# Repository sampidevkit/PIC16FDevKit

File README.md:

# PIC16F877A MICROCONTROLLER DEVELOPMENT KIT

## 1. Sơ Đồ Khối

## 2. Sơ Đồ Nguyên Lý

## 3. Vi Điều Khiển Chính PIC16F877A

## 4. Môi Trường Lập Trình, Trình Biên Dịch và Công Cụ Hỗ Trợ

### 4.1. Môi Trường Lập Trình MPLAB X IDE

### 4.2. Trình Biên Dịch MPLAB XC8

## 5. Mạch Nạp Tích Hợp

### 5.1. Nạp Chương Trình Mạch Nạp

### 5.2. Cập Nhật Chương Trình Mạch Nạp

### 5.3 Các Trạng Thái LED Lỗi

## 6. Hướng Dẫn Lập Trình Cơ Bản

## 7. Tài Liệu Kỹ Thuật:
* [PIC16F87XA Datasheet](https://ww1.microchip.com/downloads/aemDocuments/documents/MCU08/ProductDocuments/DataSheets/39582C.pdf).
* [PIC16F87XA Programming Specifications](https://ww1.microchip.com/downloads/en/DeviceDoc/39589C.pdf).

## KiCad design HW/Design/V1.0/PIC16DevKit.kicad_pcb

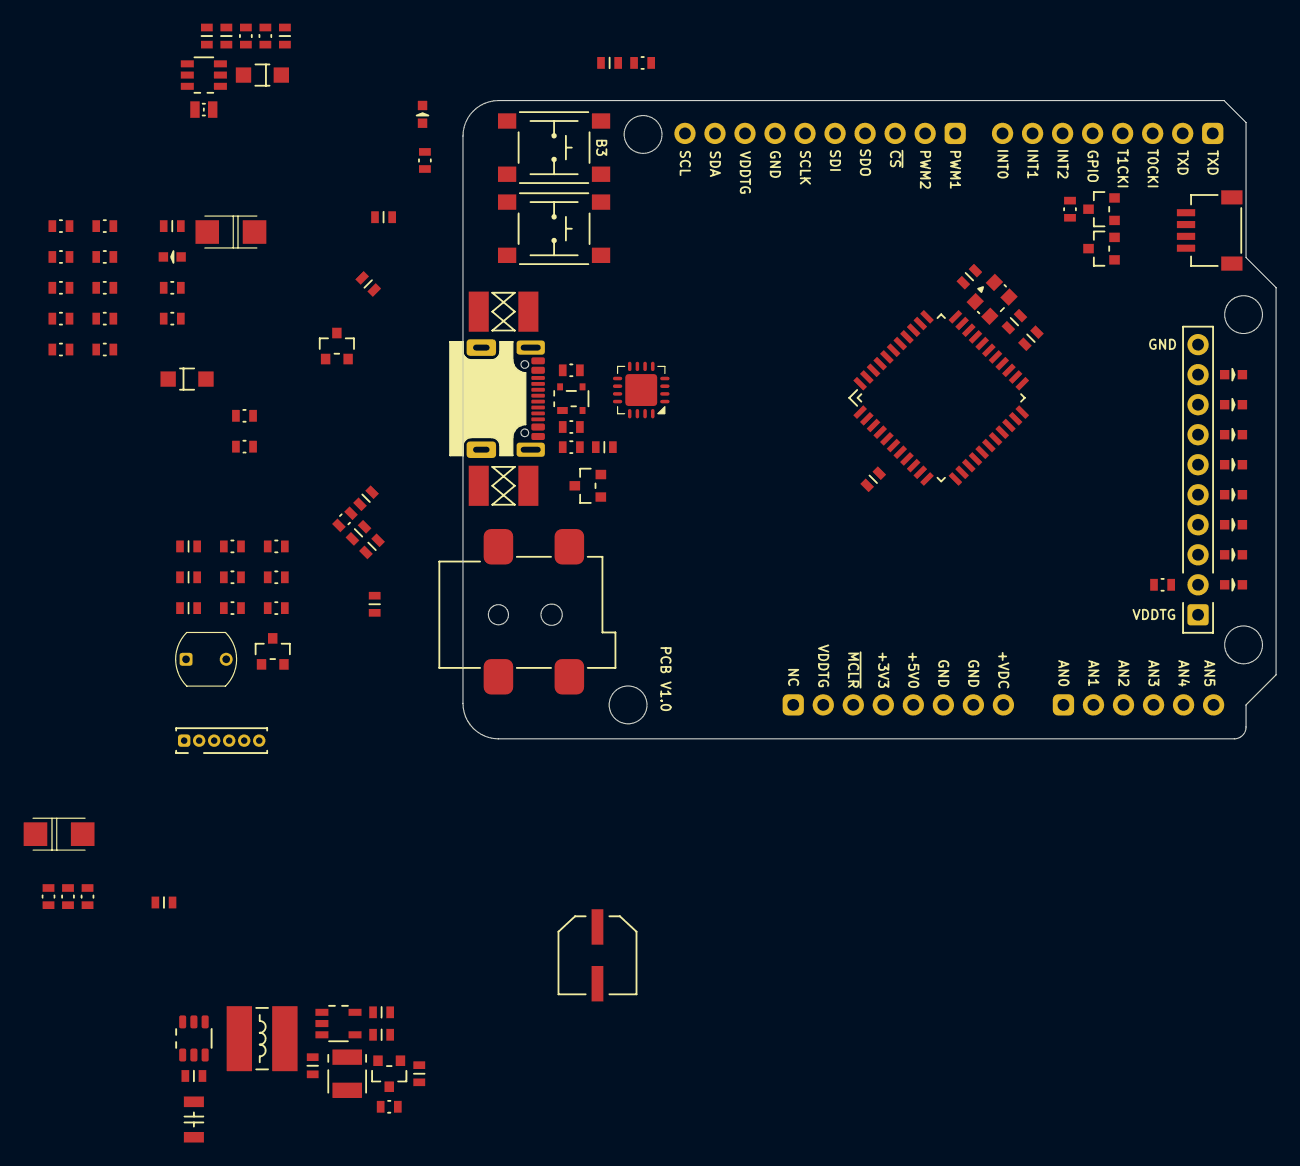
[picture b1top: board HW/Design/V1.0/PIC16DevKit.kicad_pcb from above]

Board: 4 copper layers, 68.8 x 54.0 mm, 102 parts (0 on the bottom side), 82 nets, no tracks yet.

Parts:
BT1: MODE; SW6x6-G
BT2: UBT; SW6x6-G
C1: 220uF; CAP_ELEC-6.6x6.6-DIA6.3
C2: 220uF; CAP1411
C3: 10uF; CAP1206
C4, C5, C6, C14, C17, C18, C19, C20, C22, C25, C26, C32, C37, C38: 100nF; CAP0603
C7, C8, C9, C10, C11, C13, C21, C27: 10uF; CAP0603
C12, C15, C16: 22pF; CAP0603
D1: 15V; DO-214AC
D2, D5: 200mA/0.2VF; SOD-123FL
D3: TVS 5V; SOT143B_NEXT
D4: 1A; DO-214AC
D6: SLED; LED0603
D7: POWER; LED0603
D8: D0; LED0603
D9: D1; LED0603
D10: D2; LED0603
D11: D3; LED0603
D12: D4; LED0603
D13: D5; LED0603
D14: D6; LED0603
D15: D7; LED0603
F1: 1A; FUSE1812
F2: 500mA; FUSE1812
J1: 9V-12V; PJ-002AH-SMT
J2: USB C; USB4105
J3: EXP PORT; HDM1x10x2.54_TH
J4: ICSP; HD-1x6x1.27MM-TH
J5: QWIIC; HDM-1x4x1.0-RA
L1: 10uH/1.4A; IND5852
L2: 10uH/100mA; IND0805
MD1: ARDUINO-UNO-R3
Q1, Q3: SI2301; SOT23
Q5, Q6, Q7: SI2302; SOT23
R1: 52.3K; RES0603
R2, R3, R10, R18, R26, R33: 10K; RES0603
R4: 100K; RES0603
R5: 191K; RES0603
R6, R7, R19, R20, R21, R22, R23, R27: 5.1K; RES0603
R8, R9, R11, R12, R13, R14, R15, R16, R17, R24, R25: 1K; RES0603
R28, R29, R30, R31, R32, R35: 330R; RES0603
R34: 10K; CDS-5MM
U1: LDO 3.3V/300mA; SOT-23-5_MCHP
U2: BUCK 5V/1A; SOT-23-6_MCHP
U3: BOOST 12V; SOT-23-6_MCHP
U4: PIC16F877A; TQFP44-10x10-P0.8
U5: PIC16(L)F1454; VQFN16-P0.65-4x4
U6: SOT23
U10: 20MHz; CDFN3225-4LD-PL-1

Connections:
+3.3V: C8.2, J5.2 (VDD), MD1.4 (+3V3), Q6.1 (G), Q7.1 (G), R21.2, R23.2, U1.5 (VOUT)
+5V: C2.+, C6.1, C13.2, C25.2, C26.2, D5.A, J4.2, L1.2, L2.1, MD1.5 (+5V), Q1.2 (S), Q3.2 (S), R1.2, R4.1, R25.2, U3.5 (IN), U5.16 (VDD)
+VDDTG: C7.2, C9.2, C18.1, C20.1, J3.1, MD1.2 (IOREF), MD1.30 (AREF), Q1.3 (D), R18.1, R19.2, R20.2, R22.2, R27.1, R35.1, U1.1 (VIN), U1.3 (EN), U4.7 (VDD), U4.28 (VDD)
/POWER/USB_N: D3.3 (CH2), J2.A7 (DN1), J2.B7 (DN2), U5.11 (RA1/D-/IOC/PGC2)
/POWER/USB_P: D3.2 (CH1), J2.A6 (DP1), J2.B6 (DP2), U5.12 (RA0/D+/IOC/PGD2)
/POWER/VPP_EN: U3.4 (EN), U5.1 (RA5/SOSCI/T1CKI/PWM2/IOC/CLKIN/OSC1)
/POWER/~VTG_EN: Q1.1 (G), R4.2, U5.7 (RC2/SDO)
/PROGRAMMER/PGC_SDA: J4.4, U5.8 (RC1/SDA/SDI/INT/PGC1)
/PROGRAMMER/PGD_SCL: J4.5, U5.9 (RC0/SCL/SCK/PGD1)
/TARGET MCU/MCU_TXD: R31.2, R32.2, U4.1 (DT/RX/RC7), U4.44 (CK/TX/RC6)
/TARGET MCU/PGC_SDA: MD1.31 (D14/SDA), R27.2, U4.16 (PGC/RB6)
/TARGET MCU/PGD_SCL: MD1.32 (D15/SCL), R19.1, U4.17 (PGD/RB7)
AN0: MD1.9 (AN0), U4.19 (AN0/RA0)
AN1: MD1.10 (AN1), U4.20 (AN1/RA1)
AN2: MD1.11 (AN2), U4.21 (CVREF/VREF-/AN2/RA2)
AN3: MD1.12 (AN3), U4.22 (VREF+/AN3/RA3)
AN4: MD1.13 (AN4/SDA), U4.24 (~SS/C2OUT/AN4/RA5)
AN5: MD1.14 (AN5/SCL), U4.25 (RE0/~RD/AN5)
GND: BT1.3, BT1.4, BT2.3, BT2.4, C1.-, C2.-, C3.2, C4.1, C6.2, C7.1, C8.1, C9.1, C10.1, C11.2, C13.1, C14.2, C15.2, C16.1, C17.2, C18.2, C20.2, C21.1, C22.2, C25.1, C26.1, C27.2, C32.2, C37.1, C38.2, D1.A, D3.1 (GND), D6.K, D7.K, J1.2, J1.3, J2.A1B12 (GND), J2.B1A12 (GND), J2.S1, J2.S2, J2.S3, J2.S4, J3.10, J4.3, J5.0 (EP), J5.1 (GND), MD1.6 (GND), MD1.7 (GND), MD1.29 (GND), Q5.2 (S), R2.1, R3.2, R6.2, R7.1, R9.1, R10.2, R11.1, R12.1, R13.1, R14.1, R15.1, R16.1, R17.1, R33.2, U1.2 (GND), U2.1 (GND), U3.2 (GND), U4.6 (VSS), U4.29 (VSS), U5.13 (VSS), U5.17 (EP), U6.3 (GND), U10.2 (GND1), U10.4 (X2)
GPIO: MD1.19 (D4), U4.15 (RB5)
INT0: MD1.22 (D7), U4.8 (INT/RB0)
INT1: MD1.21 (D6), U4.9 (RB1)
INT2: MD1.20 (D5), U4.10 (RB2)
unnamed: C3.1, C19.2, D1.K, D4.A, F1.2, R8.1
unnamed: D3.4 (CH3), F2.1, J2.A4B9 (VBUS), J2.B4A9 (VBUS)
unnamed: D5.K, R26.2
unnamed: D6.A, R24.1
unnamed: D7.A, R25.1
unnamed: D8.K, R17.2
unnamed: D9.K, R16.2
unnamed: D10.K, R15.2
unnamed: D11.K, R14.2
unnamed: D12.K, R13.2
unnamed: D13.K, R12.2
unnamed: D14.K, R9.2
unnamed: D15.K, R11.2
unnamed: F1.1, J1.1
unnamed: J2.A5 (CC1), R7.2
unnamed: J2.B5 (CC2), R6.1
unnamed: J5.4 (SCL), Q6.2 (S), R21.1
unnamed: J5.3 (SDA), Q7.2 (S), R23.1
unnamed: MD1.15 (D0/RXD), R32.1
unnamed: MD1.16 (D1/TXD), R31.1
unnamed: C19.1, Q3.1 (G), R3.1, R8.2, U2.5 (EN)
unnamed: C38.1, U1.4 (NC/BP)
unnamed: C5.2, U2.6 (BS)
unnamed: R1.1, R2.2, U2.4 (FB)
unnamed: C5.1, L1.1, U2.2 (SW)
unnamed: C12.2, R5.2, R10.1, U3.3 (FB)
unnamed: D2.A, L2.2, U3.1 (SW)
unnamed: R28.2, U5.5 (RC4/TX/CK)
unnamed: R30.2, U5.4 (RC5/T0CKI/RX/DT/PWM1)
unnamed: C27.1, U5.10 (VUSB3V3)
unnamed: C21.2, R34.2, R35.2, U6.1 (VDD)
unnamed: C15.1, U4.30 (OSC1/CLKI), U10.3 (GND2)
unnamed: C16.2, U4.31 (OSC2/CLKO), U10.1 (X1)
PWM1: MD1.23 (D8), U4.36 (CCP1/RC2)
PWM2: MD1.24 (D9), U4.35 (T1OSI/CCP2/RC1)
RD0: D8.A, J3.9, U4.5 (RD7/PSP7)
RD1: D9.A, J3.8, U4.4 (RD6/PSP6)
RD2: D10.A, J3.7, U4.3 (RD5/PSP5)
RD3: D11.A, J3.6, U4.2 (RD4/PSP4)
RD4: D12.A, J3.5, U4.41 (RD3/PSP3)
RD5: D13.A, J3.4, U4.40 (RD2/PSP2)
RD6: D14.A, J3.3, U4.39 (RD1/PSP1)
RD7: D15.A, J3.2, U4.38 (RD0/PSP0)
SCL: Q6.3 (D), R22.1
SCLK: MD1.28 (D13/SCLK), U4.37 (SCK/SCL/RC3)
SDA: Q7.3 (D), R20.1
SDI: MD1.27 (D12/MISO), U4.42 (SDI/SDA/RC4)
SDO: MD1.26 (D11/MOSI), U4.43 (SDO/RC5)
SLED: R24.2, U5.6 (RC3/PWM2/SS/CLKR)
T0CKI: MD1.17 (D2), U4.23 (C1OUT/T0CKI/RA4)
T1CKI: MD1.18 (D3), U4.32 (T1OSO/T1CKI/RC0)
TEMP: C14.1, C22.1, R33.1, R34.1, U4.26 (RE1/~WR/AN6), U6.2 (VOUT)
VBUS: C10.2, F2.2, Q3.3 (D)
VDC: C1.+, C4.2, D4.K, MD1.8 (VIN), U2.3 (IN)
VPP: C11.1, C12.1, D2.K, R5.1, R29.1
~CS: MD1.25 (D10/~SS), U4.14 (RB4)
~PG_MCLR: BT1.1, BT1.2, C32.1, J4.1, R26.1
~TG_MCLR: C37.2, MD1.3 (RESET), Q5.1 (G), Q5.3 (D), R29.2, U4.18 (~MCLR/VPP), U5.2 (RA4/SOSCO/T1G/SDO/IOC/CLKOUT/OSC2/CLKR)
~UBT: BT2.1, BT2.2, C17.1, R18.2, U4.11 (PGM/RB3)

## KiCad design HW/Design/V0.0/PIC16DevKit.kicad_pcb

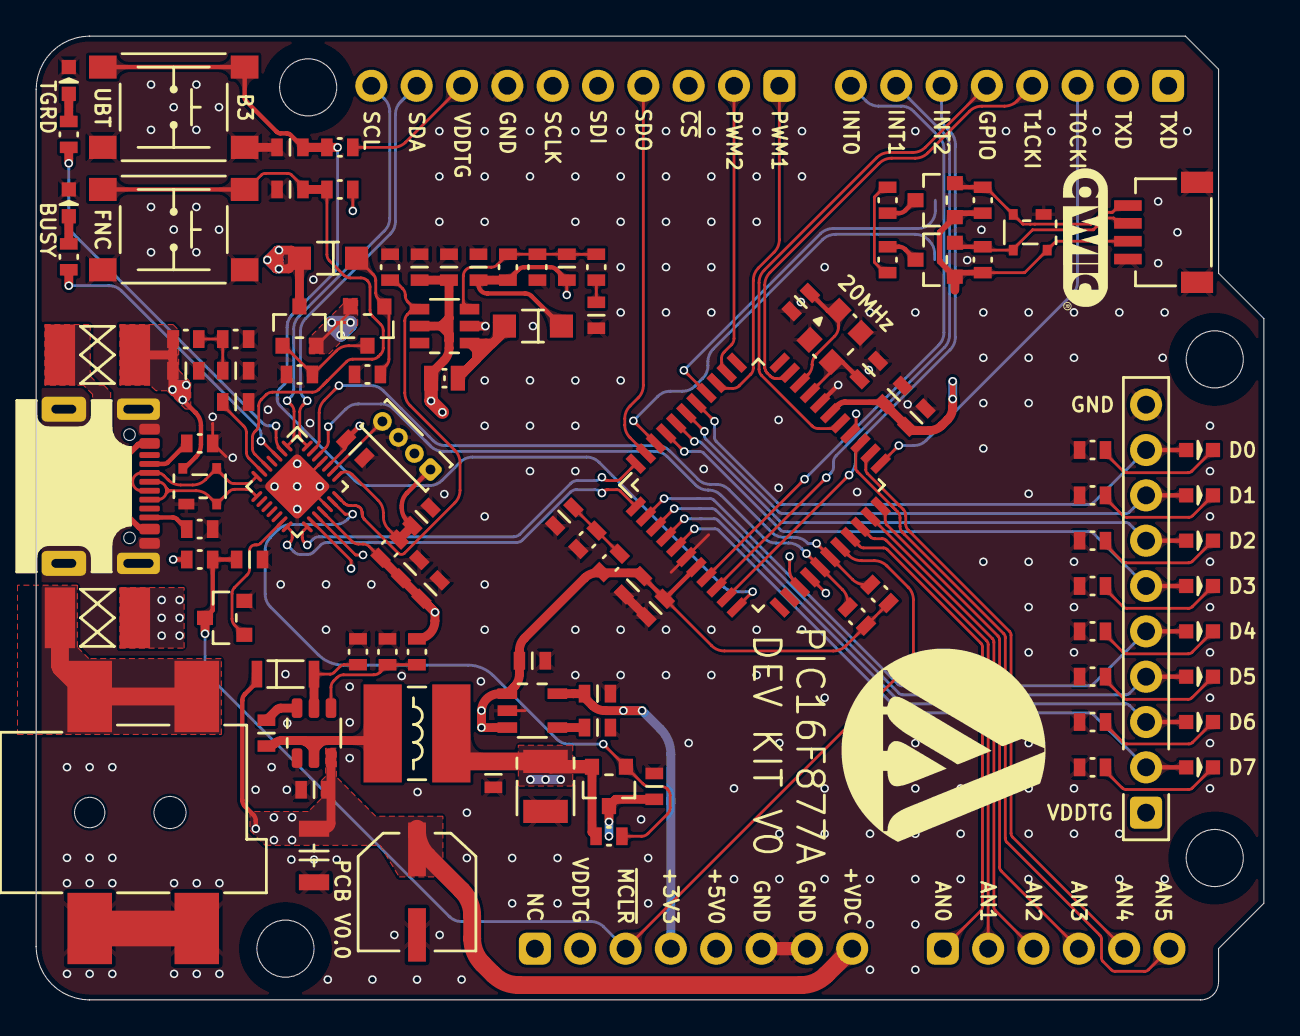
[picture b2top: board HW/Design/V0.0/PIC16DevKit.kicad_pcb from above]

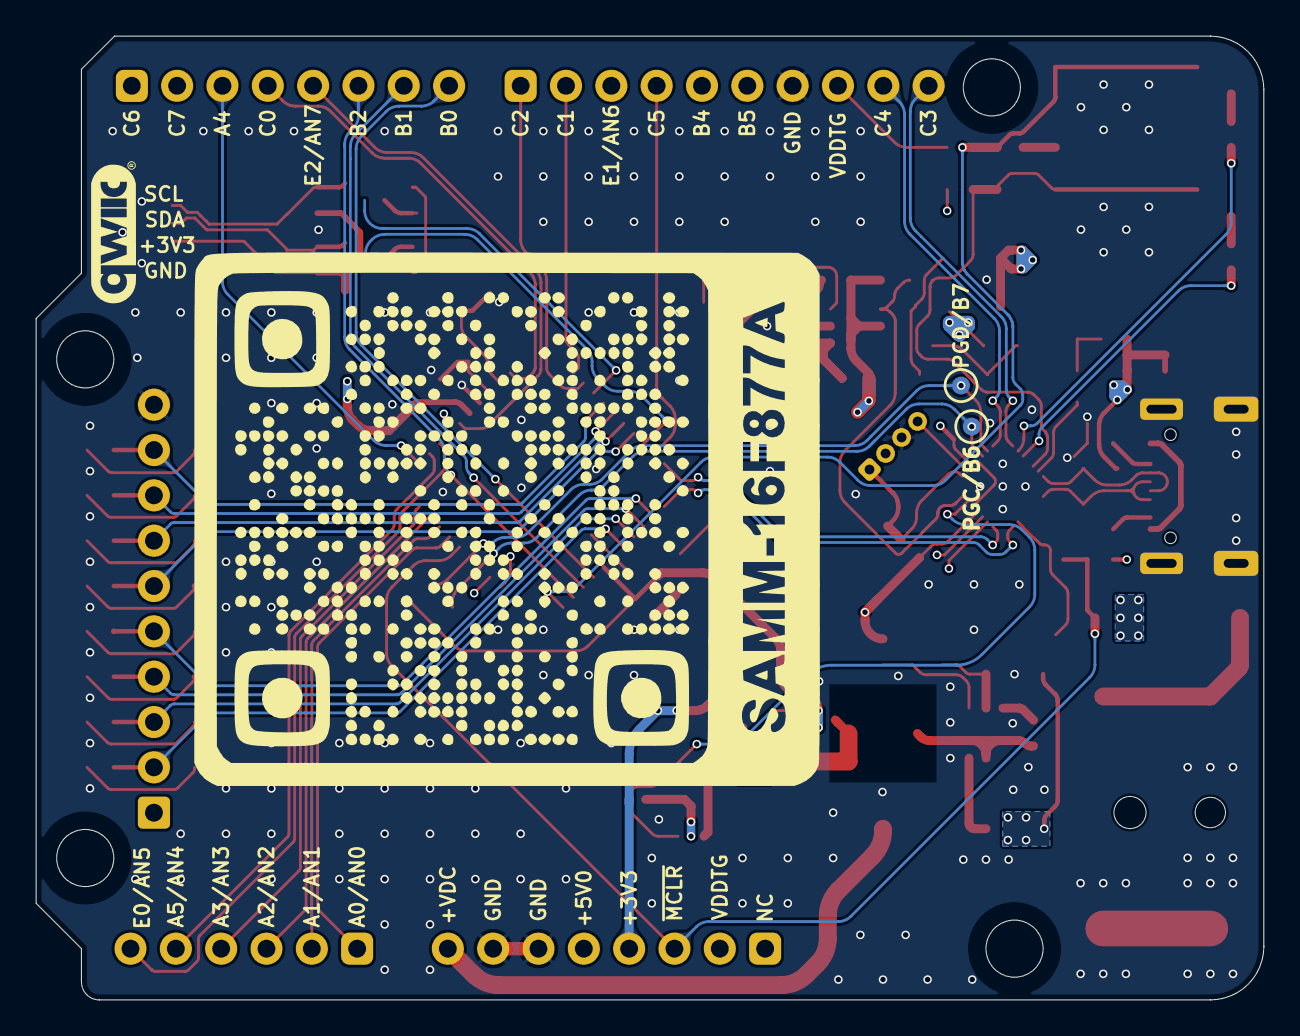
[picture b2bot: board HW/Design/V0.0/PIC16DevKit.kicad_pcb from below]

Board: 4 copper layers, 68.8 x 54.0 mm, 109 parts (2 on the bottom side), 84 nets.

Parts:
BT1: FNC; SW6x6-G
BT2: UBT; SW6x6-G
C1: 220uF; CAP_ELEC-6.6x6.6-DIA6.3
C2: 220uF; CAP1411
C3: 10uF/16V; CAP1206
C4, C5, C6, C14, C17, C18, C20, C22, C25, C26, C32, C37, C38, C39, C40, C41: 100nF; CAP0603
C7, C8, C9, C10, C11, C13, C19, C21, C27: 10uF; CAP0603
C12, C15, C16: 22pF; CAP0603
C23: 470nF; CAP0603
D1: 5V1; SOD80C-LL34
D2, D4: 200mA/0.2VF; SOD-123FL
D3, D5: TVS 5V; SOT143B_NEXT
D6: TGRD; LED0603
D7: BUSY; LED0603
D8: D0; LED0603
D9: D1; LED0603
D10: D2; LED0603
D11: D3; LED0603
D12: D4; LED0603
D13: D5; LED0603
D14: D6; LED0603
D15: D7; LED0603
F1: 1A; FUSE1812
F2: 500mA; FUSE1812
J1: 9V-12V; PJ-002AH-SMT
J2: USB C; USB4105
J3: EXP PORT; HDM1x10x2.54_TH
J4: SIL04; HD-1x4x1.27MM-TH
J5: QWIIC; HDM-1x4x1.0-RA
L1: 10uH/1.4A; IND5852
L2: 10uH/100mA; IND0805
MD1: ARDUINO-UNO-R3
Q1, Q3: SI2301; SOT23
Q4: 2N3906; SOT23
Q5, Q6, Q7: SI2302; SOT23
R1: 52.3K, 1%; RES0603
R2, R10, R36: 10K, 1%; RES0603
R3, R8, R9, R31: 100K; RES0603
R4, R18, R23, R26: 10K; RES0603
R5: 191K, 1%; RES0603
R6, R7, R19, R21, R22, R27, R28, R30, R32, R35: 5.1K, 1%; RES0603
R11, R12, R13, R14, R15, R16, R17, R20, R24, R25, R29: 330R; RES0603
R33, R34: 47K, 1%; RES0603
TP1: PGC/B6; TP1MM
TP2: PGD/B7; TP1MM
U1: LDO 3.3V/300mA; SOT-23-5_MCHP
U2: MT1470; SOT-23-6_MCHP
U3: MT3608; SOT-23-6_MCHP
U4: PIC16F877A; TQFP44-10x10-P0.8
U5: AVRxxDU28; VQFN28-4x4-EP
U10: 20MHz; CDFN3225-4LD-PL-1

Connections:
+3.3V: C8.1, D5.4 (CH3), J5.2 (VDD), MD1.4 (+3V3), Q6.1 (G), Q7.1 (G), R28.1, R30.1, U1.5 (VOUT)
+5V: C2.+, C6.1, C13.1, C14.1, C25.1, C26.1, C27.1, J4.2, L1.2, L2.1, MD1.5 (+5V), Q1.2 (S), Q3.2 (S), Q4.2 (E), R1.1, R4.1, R23.1, R26.1, U3.5 (IN), U5.18 (VDD), U5.24 (VDD)
+VDDTG: C7.1, C9.1, C18.1, C19.1, C20.1, C21.1, J3.1, MD1.2 (IOREF), MD1.30 (AREF), Q1.3 (D), R18.1, R19.1, R21.1, R22.1, R27.1, R34.1, U1.1 (VIN), U1.3 (EN), U4.7 (VDD), U4.28 (VDD)
/POWER/USB_N: D3.3 (CH2), J2.A7 (DN1), J2.B7 (DN2), U5.7 (DM)
/POWER/USB_P: D3.2 (CH1), J2.A6 (DP1), J2.B6 (DP2), U5.8 (DP)
/POWER/VBUS_DIV: C39.1, R32.1, R33.2, U5.9 (PC3/ACINP/AIN6)
/POWER/VDDTG_DIV: C40.1, R34.2, R35.1, U5.11 (PD1/AIN8)
/POWER/VPP_DIV: C41.1, R36.2, U5.10 (PD0/ACINN/AIN7)
/POWER/VPP_EN: R31.1, U3.4 (EN), U5.21 (PF1/ANI16/XTAL32K2)
/POWER/~VTG_EN: Q1.1 (G), R4.2, U5.20 (PF0/AIN15/XTAL32K1)
/PROGRAMMER/LED_BUSY: R25.1, U5.3 (PA5/MISO/A2RX0/AIN3)
/PROGRAMMER/LED_TGRDY: R24.1, U5.2 (PA4/MOSI/A2TX0/AIN2)
/PROGRAMMER/PG_UPDI: J4.4, U5.23 (PF7/UPDI)
/PROGRAMMER/RXD0: U4.44 (CK/TX/RC6), U5.15 (PD5/AMISO/A3RX0/AIN12)
/PROGRAMMER/RXD1: MD1.16 (D1/TXD), U5.17 (PD7/RX1/AINN/AIN14)
/PROGRAMMER/SCL: MD1.32 (D15/SCL), Q6.3 (D), R22.2, U4.37 (SCK/SCL/RC3), U5.1 (PA3/A1RX0/SCL/AIN1)
/PROGRAMMER/SDA: MD1.31 (D14/SDA), Q7.3 (D), R21.2, U4.42 (SDI/SDA/RC4), U5.28 (PA2/A1TX0/SDA/AIN0)
/PROGRAMMER/TG_MCLR: Q5.1 (G), U5.13 (PD3/ACINN/AIN10)
/PROGRAMMER/TG_PGC: R19.2, TP1.1, U4.16 (PGC/RB6), U5.26 (PA0/TX0/ASDA/XTALHF1)
/PROGRAMMER/TG_PGD: R27.2, TP2.1, U4.17 (PGD/RB7), U5.27 (PA1/RX0/ASCL/XTALHF2)
/PROGRAMMER/TXD0: U4.1 (DT/RX/RC7), U5.14 (PD4/AMOSI/A3TX0/AIN11)
/PROGRAMMER/TXD1: MD1.15 (D0/RXD), U5.16 (PD6/ASCLK/TX1/ACINP/AIN13)
/PROGRAMMER/~BT_FNC: BT1.1, BT1.2, C22.1, R23.2, U5.5 (PA7/ACOUT/AIN5)
/PROGRAMMER/~PG_RESET: C32.2, J4.1, R26.2, U5.22 (PF6/~RESET)
/PROGRAMMER/~TG_MCLR: C37.1, MD1.3 (RESET), Q5.3 (D), R29.2, U4.18 (~MCLR/VPP)
/TARGET MCU/AN0: MD1.9 (AN0), U4.19 (AN0/RA0)
/TARGET MCU/AN1: MD1.10 (AN1), U4.20 (AN1/RA1)
/TARGET MCU/AN2: MD1.11 (AN2), U4.21 (CVREF/VREF-/AN2/RA2)
/TARGET MCU/AN3: MD1.12 (AN3), U4.22 (VREF+/AN3/RA3)
/TARGET MCU/AN4: MD1.13 (AN4/SDA), U4.24 (~SS/C2OUT/AN4/RA5)
/TARGET MCU/AN5: MD1.14 (AN5/SCL), U4.25 (RE0/~RD/AN5)
/TARGET MCU/GPIO: MD1.19 (D4), U4.27 (RE2/~CS/AN7)
/TARGET MCU/INT0: MD1.22 (D7), U4.8 (INT/RB0)
/TARGET MCU/INT1: MD1.21 (D6), U4.9 (RB1)
/TARGET MCU/INT2: MD1.20 (D5), U4.10 (RB2)
/TARGET MCU/PWM1: MD1.23 (D8), U4.36 (CCP1/RC2)
/TARGET MCU/PWM2: MD1.24 (D9), U4.35 (T1OSI/CCP2/RC1)
/TARGET MCU/RD0: D8.A, J3.9, U4.38 (RD0/PSP0)
/TARGET MCU/RD1: D9.A, J3.8, U4.39 (RD1/PSP1)
/TARGET MCU/RD2: D10.A, J3.7, U4.40 (RD2/PSP2)
/TARGET MCU/RD3: D11.A, J3.6, U4.41 (RD3/PSP3)
/TARGET MCU/RD4: D12.A, J3.5, U4.2 (RD4/PSP4)
/TARGET MCU/RD5: D13.A, J3.4, U4.3 (RD5/PSP5)
/TARGET MCU/RD6: D14.A, J3.3, U4.4 (RD6/PSP6)
/TARGET MCU/RD7: D15.A, J3.2, U4.5 (RD7/PSP7)
/TARGET MCU/SCLK: MD1.28 (D13/SCLK), U4.15 (RB5)
/TARGET MCU/SDI: MD1.27 (D12/MISO), U4.14 (RB4)
/TARGET MCU/SDO: MD1.26 (D11/MOSI), U4.43 (SDO/RC5)
/TARGET MCU/T0CKI: MD1.17 (D2), U4.23 (C1OUT/T0CKI/RA4)
/TARGET MCU/T1CKI: MD1.18 (D3), U4.32 (T1OSO/T1CKI/RC0)
/TARGET MCU/~CS: MD1.25 (D10/~SS), U4.26 (RE1/~WR/AN6)
/TARGET MCU/~UBT: BT2.1, BT2.2, C17.2, R18.2, U4.11 (PGM/RB3)
GND: BT1.3, BT1.4, BT2.3, BT2.4, C1.-, C2.-, C3.2, C4.2, C6.2, C7.2, C8.2, C9.2, C10.2, C11.2, C13.2, C14.2, C15.1, C16.1, C17.1, C18.2, C19.2, C20.2, C21.2, C22.2, C23.2, C25.2, C26.2, C27.2, C32.1, C37.2, C38.2, C39.2, C40.2, C41.2, D3.1 (GND), D5.1 (GND), D6.K, D7.K, J1.2, J1.3, J2.A1B12 (GND), J2.B1A12 (GND), J2.S1, J2.S2, J2.S3, J2.S4, J3.10, J4.3, J5.0 (EP), J5.1 (GND), MD1.6 (GND), MD1.7 (GND), MD1.29 (GND), Q5.2 (S), R2.2, R3.2, R6.2, R7.2, R8.2, R9.2, R10.2, R11.1, R12.1, R13.1, R14.1, R15.1, R16.1, R17.1, R20.1, R31.2, R32.2, R35.2, U1.2 (GND), U2.1 (GND), U3.2 (GND), U4.6 (VSS), U4.29 (VSS), U5.19 (GND), U5.25 (GND), U5.29 (EP), U10.2 (GND1), U10.4 (X2)
unnamed: D5.2 (CH1), J5.4 (SCL), Q6.2 (S), R28.2
unnamed: D5.3 (CH2), J5.3 (SDA), Q7.2 (S), R30.2
unnamed: D6.A, R24.2
unnamed: D7.A, R25.2
unnamed: D8.K, R20.2
unnamed: D9.K, R17.2
unnamed: D10.K, R16.2
unnamed: D11.K, R15.2
unnamed: D12.K, R14.2
unnamed: D13.K, R13.2
unnamed: D14.K, R12.2
unnamed: D15.K, R11.2
unnamed: F1.1, J1.1
unnamed: F2.1, J2.A4B9 (VBUS), J2.B4A9 (VBUS)
unnamed: J2.A5 (CC1), R7.1
unnamed: J2.B5 (CC2), R6.1
unnamed: Q3.1 (G), Q4.3 (C), R9.1
unnamed: D4.K, Q4.1 (B), R8.1
unnamed: C38.1, U1.4 (NC/BP)
unnamed: C5.2, U2.6 (BS)
unnamed: D1.A, R3.1, U2.5 (EN)
unnamed: R1.2, R2.1, U2.4 (FB)
unnamed: C5.1, L1.1, U2.2 (SW)
unnamed: C12.2, R5.2, R10.1, R36.1, U3.3 (FB)
unnamed: D2.A, L2.2, U3.1 (SW)
unnamed: C23.1, U5.6 (VUSB)
unnamed: C15.2, U4.30 (OSC1/CLKI), U10.3 (GND2)
unnamed: C16.2, U4.31 (OSC2/CLKO), U10.1 (X1)
VBUS: C10.1, D3.4 (CH3), D4.A, F2.2, Q3.3 (D), R33.1
VDC: C1.+, C3.1, C4.1, D1.K, F1.2, MD1.8 (VIN), U2.3 (IN)
VPP: C11.1, C12.1, D2.K, R5.1, R29.1

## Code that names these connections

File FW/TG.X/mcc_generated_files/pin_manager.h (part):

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#define RA0_SetHigh()            do { LATAbits.LATA0 = 1; } while(0)
#define RA0_SetLow()             do { LATAbits.LATA0 = 0; } while(0)
#define RA0_Toggle()             do { LATAbits.LATA0 = ~LATAbits.LATA0; } while(0)
#define RA0_GetValue()              PORTAbits.RA0
#define RA0_SetDigitalInput()    do { TRISAbits.TRISA0 = 1; } while(0)
#define RA0_SetDigitalOutput()   do { TRISAbits.TRISA0 = 0; } while(0)
#define RA0_SetPullup()             do { WPUAbits.WPUA0 = 1; } while(0)
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#define RA1_SetHigh()            do { LATAbits.LATA1 = 1; } while(0)
#define RA1_SetLow()             do { LATAbits.LATA1 = 0; } while(0)
#define RA1_Toggle()             do { LATAbits.LATA1 = ~LATAbits.LATA1; } while(0)
#define RA1_GetValue()              PORTAbits.RA1
#define RA1_SetDigitalInput()    do { TRISAbits.TRISA1 = 1; } while(0)
#define RA1_SetDigitalOutput()   do { TRISAbits.TRISA1 = 0; } while(0)
#define RA1_SetPullup()             do { WPUAbits.WPUA1 = 1; } while(0)
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// get/set ULED aliases
#define ULED_TRIS                 TRISAbits.TRISA2
#define ULED_LAT                  LATAbits.LATA2
#define ULED_PORT                 PORTAbits.RA2
#define ULED_WPU                  WPUAbits.WPUA2
#define ULED_OD                   ODCONAbits.ODA2
#define ULED_ANS                  ANSELAbits.ANSA2
#define ULED_SetHigh()            do { LATAbits.LATA2 = 1; } while(0)
#define ULED_SetLow()             do { LATAbits.LATA2 = 0; } while(0)
#define ULED_Toggle()             do { LATAbits.LATA2 = ~LATAbits.LATA2; } while(0)
#define ULED_GetValue()           PORTAbits.RA2
#define ULED_SetDigitalInput()    do { TRISAbits.TRISA2 = 1; } while(0)
#define ULED_SetDigitalOutput()   do { TRISAbits.TRISA2 = 0; } while(0)
#define ULED_SetPullup()          do { WPUAbits.WPUA2 = 1; } while(0)
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#define RA4_SetHigh()            do { LATAbits.LATA4 = 1; } while(0)
#define RA4_SetLow()             do { LATAbits.LATA4 = 0; } while(0)
#define RA4_Toggle()             do { LATAbits.LATA4 = ~LATAbits.LATA4; } while(0)
#define RA4_GetValue()              PORTAbits.RA4
#define RA4_SetDigitalInput()    do { TRISAbits.TRISA4 = 1; } while(0)
#define RA4_SetDigitalOutput()   do { TRISAbits.TRISA4 = 0; } while(0)
#define RA4_SetPullup()             do { WPUAbits.WPUA4 = 1; } while(0)
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#define RA5_SetHigh()            do { LATAbits.LATA5 = 1; } while(0)
#define RA5_SetLow()             do { LATAbits.LATA5 = 0; } while(0)
#define RA5_Toggle()             do { LATAbits.LATA5 = ~LATAbits.LATA5; } while(0)
#define RA5_GetValue()              PORTAbits.RA5
#define RA5_SetDigitalInput()    do { TRISAbits.TRISA5 = 1; } while(0)
#define RA5_SetDigitalOutput()   do { TRISAbits.TRISA5 = 0; } while(0)
#define RA5_SetPullup()             do { WPUAbits.WPUA5 = 1; } while(0)
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// get/set SCK aliases
#define SCK_TRIS                 TRISBbits.TRISB4
#define SCK_LAT                  LATBbits.LATB4
#define SCK_PORT                 PORTBbits.RB4
#define SCK_WPU                  WPUBbits.WPUB4
#define SCK_OD                   ODCONBbits.ODB4
#define SCK_ANS                  ANSELBbits.ANSB4
#define SCK_SetHigh()            do { LATBbits.LATB4 = 1; } while(0)
#define SCK_SetLow()             do { LATBbits.LATB4 = 0; } while(0)
#define SCK_Toggle()             do { LATBbits.LATB4 = ~LATBbits.LATB4; } while(0)
#define SCK_GetValue()           PORTBbits.RB4
#define SCK_SetDigitalInput()    do { TRISBbits.TRISB4 = 1; } while(0)
#define SCK_SetDigitalOutput()   do { TRISBbits.TRISB4 = 0; } while(0)
#define SCK_SetPullup()          do { WPUBbits.WPUB4 = 1; } while(0)
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#define RB5_SetHigh()            do { LATBbits.LATB5 = 1; } while(0)
#define RB5_SetLow()             do { LATBbits.LATB5 = 0; } while(0)
#define RB5_Toggle()             do { LATBbits.LATB5 = ~LATBbits.LATB5; } while(0)
#define RB5_GetValue()              PORTBbits.RB5
#define RB5_SetDigitalInput()    do { TRISBbits.TRISB5 = 1; } while(0)
#define RB5_SetDigitalOutput()   do { TRISBbits.TRISB5 = 0; } while(0)
#define RB5_SetPullup()             do { WPUBbits.WPUB5 = 1; } while(0)
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#define RB6_SetHigh()            do { LATBbits.LATB6 = 1; } while(0)
#define RB6_SetLow()             do { LATBbits.LATB6 = 0; } while(0)
#define RB6_Toggle()             do { LATBbits.LATB6 = ~LATBbits.LATB6; } while(0)
#define RB6_GetValue()              PORTBbits.RB6
#define RB6_SetDigitalInput()    do { TRISBbits.TRISB6 = 1; } while(0)
#define RB6_SetDigitalOutput()   do { TRISBbits.TRISB6 = 0; } while(0)
#define RB6_SetPullup()             do { WPUBbits.WPUB6 = 1; } while(0)
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// get/set GPIO1 aliases
#define GPIO1_TRIS                 TRISBbits.TRISB7
#define GPIO1_LAT                  LATBbits.LATB7
#define GPIO1_PORT                 PORTBbits.RB7
#define GPIO1_WPU                  WPUBbits.WPUB7
#define GPIO1_OD                   ODCONBbits.ODB7
#define GPIO1_ANS                  ANSELBbits.ANSB7
#define GPIO1_SetHigh()            do { LATBbits.LATB7 = 1; } while(0)
#define GPIO1_SetLow()             do { LATBbits.LATB7 = 0; } while(0)
#define GPIO1_Toggle()             do { LATBbits.LATB7 = ~LATBbits.LATB7; } while(0)
#define GPIO1_GetValue()           PORTBbits.RB7
#define GPIO1_SetDigitalInput()    do { TRISBbits.TRISB7 = 1; } while(0)
#define GPIO1_SetDigitalOutput()   do { TRISBbits.TRISB7 = 0; } while(0)
#define GPIO1_SetPullup()          do { WPUBbits.WPUB7 = 1; } while(0)
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// get/set NCS aliases
#define NCS_TRIS                 TRISCbits.TRISC0
#define NCS_LAT                  LATCbits.LATC0
#define NCS_PORT                 PORTCbits.RC0
#define NCS_WPU                  WPUCbits.WPUC0
#define NCS_OD                   ODCONCbits.ODC0
#define NCS_ANS                  ANSELCbits.ANSC0
#define NCS_SetHigh()            do { LATCbits.LATC0 = 1; } while(0)
#define NCS_SetLow()             do { LATCbits.LATC0 = 0; } while(0)
#define NCS_Toggle()             do { LATCbits.LATC0 = ~LATCbits.LATC0; } while(0)
#define NCS_GetValue()           PORTCbits.RC0
#define NCS_SetDigitalInput()    do { TRISCbits.TRISC0 = 1; } while(0)
#define NCS_SetDigitalOutput()   do { TRISCbits.TRISC0 = 0; } while(0)
#define NCS_SetPullup()          do { WPUCbits.WPUC0 = 1; } while(0)
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// get/set SDO aliases
#define SDO_TRIS                 TRISCbits.TRISC1
#define SDO_LAT                  LATCbits.LATC1
#define SDO_PORT                 PORTCbits.RC1
#define SDO_WPU                  WPUCbits.WPUC1
#define SDO_OD                   ODCONCbits.ODC1
#define SDO_ANS                  ANSELCbits.ANSC1
#define SDO_SetHigh()            do { LATCbits.LATC1 = 1; } while(0)
#define SDO_SetLow()             do { LATCbits.LATC1 = 0; } while(0)
#define SDO_Toggle()             do { LATCbits.LATC1 = ~LATCbits.LATC1; } while(0)
#define SDO_GetValue()           PORTCbits.RC1
#define SDO_SetDigitalInput()    do { TRISCbits.TRISC1 = 1; } while(0)
#define SDO_SetDigitalOutput()   do { TRISCbits.TRISC1 = 0; } while(0)
#define SDO_SetPullup()          do { WPUCbits.WPUC1 = 1; } while(0)
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// get/set SDI aliases
#define SDI_TRIS                 TRISCbits.TRISC2
#define SDI_LAT                  LATCbits.LATC2
#define SDI_PORT                 PORTCbits.RC2
#define SDI_WPU                  WPUCbits.WPUC2
#define SDI_OD                   ODCONCbits.ODC2
#define SDI_ANS                  ANSELCbits.ANSC2
#define SDI_SetHigh()            do { LATCbits.LATC2 = 1; } while(0)
#define SDI_SetLow()             do { LATCbits.LATC2 = 0; } while(0)
#define SDI_Toggle()             do { LATCbits.LATC2 = ~LATCbits.LATC2; } while(0)
#define SDI_GetValue()           PORTCbits.RC2
#define SDI_SetDigitalInput()    do { TRISCbits.TRISC2 = 1; } while(0)
#define SDI_SetDigitalOutput()   do { TRISCbits.TRISC2 = 0; } while(0)
#define SDI_SetPullup()          do { WPUCbits.WPUC2 = 1; } while(0)
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// get/set SAN0 aliases
#define SAN0_TRIS                 TRISCbits.TRISC3
#define SAN0_LAT                  LATCbits.LATC3
#define SAN0_PORT                 PORTCbits.RC3
#define SAN0_WPU                  WPUCbits.WPUC3
#define SAN0_OD                   ODCONCbits.ODC3
#define SAN0_ANS                  ANSELCbits.ANSC3
#define SAN0_SetHigh()            do { LATCbits.LATC3 = 1; } while(0)
#define SAN0_SetLow()             do { LATCbits.LATC3 = 0; } while(0)
#define SAN0_Toggle()             do { LATCbits.LATC3 = ~LATCbits.LATC3; } while(0)
#define SAN0_GetValue()           PORTCbits.RC3
#define SAN0_SetDigitalInput()    do { TRISCbits.TRISC3 = 1; } while(0)
#define SAN0_SetDigitalOutput()   do { TRISCbits.TRISC3 = 0; } while(0)
#define SAN0_SetPullup()          do { WPUCbits.WPUC3 = 1; } while(0)
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// get/set GPIO3 aliases
#define GPIO3_TRIS                 TRISCbits.TRISC4
#define GPIO3_LAT                  LATCbits.LATC4
#define GPIO3_PORT                 PORTCbits.RC4
#define GPIO3_WPU                  WPUCbits.WPUC4
#define GPIO3_OD                   ODCONCbits.ODC4
#define GPIO3_SetHigh()            do { LATCbits.LATC4 = 1; } while(0)
#define GPIO3_SetLow()             do { LATCbits.LATC4 = 0; } while(0)
#define GPIO3_Toggle()             do { LATCbits.LATC4 = ~LATCbits.LATC4; } while(0)
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
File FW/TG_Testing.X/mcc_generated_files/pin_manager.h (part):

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// get/set BLED aliases
#define BLED_TRIS                 TRISAbits.TRISA1
#define BLED_LAT                  LATAbits.LATA1
#define BLED_PORT                 PORTAbits.RA1
#define BLED_WPU                  WPUAbits.WPUA1
#define BLED_OD                   ODCONAbits.ODCA1
#define BLED_ANS                  ANSELAbits.ANSA1
#define BLED_SetHigh()            do { LATAbits.LATA1 = 1; } while(0)
#define BLED_SetLow()             do { LATAbits.LATA1 = 0; } while(0)
#define BLED_Toggle()             do { LATAbits.LATA1 = ~LATAbits.LATA1; } while(0)
#define BLED_GetValue()           PORTAbits.RA1
#define BLED_SetDigitalInput()    do { TRISAbits.TRISA1 = 1; } while(0)
#define BLED_SetDigitalOutput()   do { TRISAbits.TRISA1 = 0; } while(0)
#define BLED_SetPullup()          do { WPUAbits.WPUA1 = 1; } while(0)
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// get/set RTC_INT aliases
#define RTC_INT_TRIS                 TRISAbits.TRISA3
#define RTC_INT_LAT                  LATAbits.LATA3
#define RTC_INT_PORT                 PORTAbits.RA3
#define RTC_INT_WPU                  WPUAbits.WPUA3
#define RTC_INT_OD                   ODCONAbits.ODCA3
#define RTC_INT_ANS                  ANSELAbits.ANSA3
#define RTC_INT_SetHigh()            do { LATAbits.LATA3 = 1; } while(0)
#define RTC_INT_SetLow()             do { LATAbits.LATA3 = 0; } while(0)
#define RTC_INT_Toggle()             do { LATAbits.LATA3 = ~LATAbits.LATA3; } while(0)
#define RTC_INT_GetValue()           PORTAbits.RA3
#define RTC_INT_SetDigitalInput()    do { TRISAbits.TRISA3 = 1; } while(0)
#define RTC_INT_SetDigitalOutput()   do { TRISAbits.TRISA3 = 0; } while(0)
#define RTC_INT_SetPullup()          do { WPUAbits.WPUA3 = 1; } while(0)
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// get/set FLASH_nCS aliases
#define FLASH_nCS_TRIS                 TRISBbits.TRISB0
#define FLASH_nCS_LAT                  LATBbits.LATB0
#define FLASH_nCS_PORT                 PORTBbits.RB0
#define FLASH_nCS_WPU                  WPUBbits.WPUB0
#define FLASH_nCS_OD                   ODCONBbits.ODCB0
#define FLASH_nCS_ANS                  ANSELBbits.ANSB0
#define FLASH_nCS_SetHigh()            do { LATBbits.LATB0 = 1; } while(0)
#define FLASH_nCS_SetLow()             do { LATBbits.LATB0 = 0; } while(0)
#define FLASH_nCS_Toggle()             do { LATBbits.LATB0 = ~LATBbits.LATB0; } while(0)
#define FLASH_nCS_GetValue()           PORTBbits.RB0
#define FLASH_nCS_SetDigitalInput()    do { TRISBbits.TRISB0 = 1; } while(0)
#define FLASH_nCS_SetDigitalOutput()   do { TRISBbits.TRISB0 = 0; } while(0)
#define FLASH_nCS_SetPullup()          do { WPUBbits.WPUB0 = 1; } while(0)
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#define RB3_SetHigh()            do { LATBbits.LATB3 = 1; } while(0)
#define RB3_SetLow()             do { LATBbits.LATB3 = 0; } while(0)
#define RB3_Toggle()             do { LATBbits.LATB3 = ~LATBbits.LATB3; } while(0)
#define RB3_GetValue()              PORTBbits.RB3
#define RB3_SetDigitalInput()    do { TRISBbits.TRISB3 = 1; } while(0)
#define RB3_SetDigitalOutput()   do { TRISBbits.TRISB3 = 0; } while(0)
#define RB3_SetPullup()             do { WPUBbits.WPUB3 = 1; } while(0)
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#define RB4_SetHigh()            do { LATBbits.LATB4 = 1; } while(0)
#define RB4_SetLow()             do { LATBbits.LATB4 = 0; } while(0)
#define RB4_Toggle()             do { LATBbits.LATB4 = ~LATBbits.LATB4; } while(0)
#define RB4_GetValue()              PORTBbits.RB4
#define RB4_SetDigitalInput()    do { TRISBbits.TRISB4 = 1; } while(0)
#define RB4_SetDigitalOutput()   do { TRISBbits.TRISB4 = 0; } while(0)
#define RB4_SetPullup()             do { WPUBbits.WPUB4 = 1; } while(0)
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#define RB5_SetHigh()            do { LATBbits.LATB5 = 1; } while(0)
#define RB5_SetLow()             do { LATBbits.LATB5 = 0; } while(0)
#define RB5_Toggle()             do { LATBbits.LATB5 = ~LATBbits.LATB5; } while(0)
#define RB5_GetValue()              PORTBbits.RB5
#define RB5_SetDigitalInput()    do { TRISBbits.TRISB5 = 1; } while(0)
#define RB5_SetDigitalOutput()   do { TRISBbits.TRISB5 = 0; } while(0)
#define RB5_SetPullup()             do { WPUBbits.WPUB5 = 1; } while(0)
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#define RB6_SetHigh()            do { LATBbits.LATB6 = 1; } while(0)
#define RB6_SetLow()             do { LATBbits.LATB6 = 0; } while(0)
#define RB6_Toggle()             do { LATBbits.LATB6 = ~LATBbits.LATB6; } while(0)
#define RB6_GetValue()              PORTBbits.RB6
#define RB6_SetDigitalInput()    do { TRISBbits.TRISB6 = 1; } while(0)
#define RB6_SetDigitalOutput()   do { TRISBbits.TRISB6 = 0; } while(0)
#define RB6_SetPullup()             do { WPUBbits.WPUB6 = 1; } while(0)
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#define RB7_SetHigh()            do { LATBbits.LATB7 = 1; } while(0)
#define RB7_SetLow()             do { LATBbits.LATB7 = 0; } while(0)
#define RB7_Toggle()             do { LATBbits.LATB7 = ~LATBbits.LATB7; } while(0)
#define RB7_GetValue()              PORTBbits.RB7
#define RB7_SetDigitalInput()    do { TRISBbits.TRISB7 = 1; } while(0)
#define RB7_SetDigitalOutput()   do { TRISBbits.TRISB7 = 0; } while(0)
#define RB7_SetPullup()             do { WPUBbits.WPUB7 = 1; } while(0)
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// get/set VDDSS_nEN aliases
#define VDDSS_nEN_TRIS                 TRISDbits.TRISD0
#define VDDSS_nEN_LAT                  LATDbits.LATD0
#define VDDSS_nEN_PORT                 PORTDbits.RD0
#define VDDSS_nEN_WPU                  WPUDbits.WPUD0
#define VDDSS_nEN_OD                   ODCONDbits.ODCD0
#define VDDSS_nEN_ANS                  ANSELDbits.ANSD0
#define VDDSS_nEN_SetHigh()            do { LATDbits.LATD0 = 1; } while(0)
#define VDDSS_nEN_SetLow()             do { LATDbits.LATD0 = 0; } while(0)
#define VDDSS_nEN_Toggle()             do { LATDbits.LATD0 = ~LATDbits.LATD0; } while(0)
#define VDDSS_nEN_GetValue()           PORTDbits.RD0
#define VDDSS_nEN_SetDigitalInput()    do { TRISDbits.TRISD0 = 1; } while(0)
#define VDDSS_nEN_SetDigitalOutput()   do { TRISDbits.TRISD0 = 0; } while(0)
#define VDDSS_nEN_SetPullup()          do { WPUDbits.WPUD0 = 1; } while(0)
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// get/set TEMP aliases
#define TEMP_TRIS                 TRISDbits.TRISD1
#define TEMP_LAT                  LATDbits.LATD1
#define TEMP_PORT                 PORTDbits.RD1
#define TEMP_WPU                  WPUDbits.WPUD1
#define TEMP_OD                   ODCONDbits.ODCD1
#define TEMP_ANS                  ANSELDbits.ANSD1
#define TEMP_SetHigh()            do { LATDbits.LATD1 = 1; } while(0)
#define TEMP_SetLow()             do { LATDbits.LATD1 = 0; } while(0)
#define TEMP_Toggle()             do { LATDbits.LATD1 = ~LATDbits.LATD1; } while(0)
#define TEMP_GetValue()           PORTDbits.RD1
#define TEMP_SetDigitalInput()    do { TRISDbits.TRISD1 = 1; } while(0)
#define TEMP_SetDigitalOutput()   do { TRISDbits.TRISD1 = 0; } while(0)
#define TEMP_SetPullup()          do { WPUDbits.WPUD1 = 1; } while(0)
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// get/set UBT aliases
#define UBT_TRIS                 TRISDbits.TRISD3
#define UBT_LAT                  LATDbits.LATD3
#define UBT_PORT                 PORTDbits.RD3
#define UBT_WPU                  WPUDbits.WPUD3
#define UBT_OD                   ODCONDbits.ODCD3
#define UBT_ANS                  ANSELDbits.ANSD3
#define UBT_SetHigh()            do { LATDbits.LATD3 = 1; } while(0)
#define UBT_SetLow()             do { LATDbits.LATD3 = 0; } while(0)
#define UBT_Toggle()             do { LATDbits.LATD3 = ~LATDbits.LATD3; } while(0)
#define UBT_GetValue()           PORTDbits.RD3
#define UBT_SetDigitalInput()    do { TRISDbits.TRISD3 = 1; } while(0)
#define UBT_SetDigitalOutput()   do { TRISDbits.TRISD3 = 0; } while(0)
#define UBT_SetPullup()          do { WPUDbits.WPUD3 = 1; } while(0)
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#define RD6_SetHigh()            do { LATDbits.LATD6 = 1; } while(0)
#define RD6_SetLow()             do { LATDbits.LATD6 = 0; } while(0)
#define RD6_Toggle()             do { LATDbits.LATD6 = ~LATDbits.LATD6; } while(0)
#define RD6_GetValue()              PORTDbits.RD6
#define RD6_SetDigitalInput()    do { TRISDbits.TRISD6 = 1; } while(0)
#define RD6_SetDigitalOutput()   do { TRISDbits.TRISD6 = 0; } while(0)
#define RD6_SetPullup()             do { WPUDbits.WPUD6 = 1; } while(0)
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#define RD7_SetHigh()            do { LATDbits.LATD7 = 1; } while(0)
#define RD7_SetLow()             do { LATDbits.LATD7 = 0; } while(0)
#define RD7_Toggle()             do { LATDbits.LATD7 = ~LATDbits.LATD7; } while(0)
#define RD7_GetValue()              PORTDbits.RD7
#define RD7_SetDigitalInput()    do { TRISDbits.TRISD7 = 1; } while(0)
#define RD7_SetDigitalOutput()   do { TRISDbits.TRISD7 = 0; } while(0)
#define RD7_SetPullup()             do { WPUDbits.WPUD7 = 1; } while(0)
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   @Returns
    none
   @Description
    GPIO and peripheral I/O initialization
   @Example
    PIN_MANAGER_Initialize();
 */
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
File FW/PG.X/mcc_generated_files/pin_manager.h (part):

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*/
/**
  @Summary
    Sets the GPIO pin, RA0, high using LATA0.

  @Description
    Sets the GPIO pin, RA0, high using LATA0.

  @Preconditions
    The RA0 must be set to an output.
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#define RFU_A0_SetHigh()          ( LATASET = (1 << 0) )
/**
  @Summary
    Sets the GPIO pin, RA0, low using LATA0.

  @Description
    Sets the GPIO pin, RA0, low using LATA0.

  @Preconditions
    The RA0 must be set to an output.
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
/**
  @Summary
    Sets a value to the GPIO pin.

  @Description
    Sets or Resets the GPIO pin, RA0, low or high using LATA0.

  @Preconditions
    The RA0 must be set to an output.
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    None.

  @Param
    bool value; : value to be set to the GPIO pin.

  @Example
    <code>
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
/**
  @Summary
    Toggles the GPIO pin, RA0, using LATA0.

  @Description
    Toggles the GPIO pin, RA0, using LATA0.

  @Preconditions
    The RA0 must be set to an output.
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#define RFU_A0_Toggle()           ( LATAINV = (1 << 0) )
/**
  @Summary
    Reads the value of the GPIO pin, RA0.

  @Description
    Reads the value of the GPIO pin, RA0.

  @Preconditions
    None.
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    </code>

*/
#define RFU_A0_GetValue()         PORTAbits.RA0
/**
  @Summary
    Configures the GPIO pin, RA0, as an input.

  @Description
    Configures the GPIO pin, RA0, as an input.

  @Preconditions
    None.
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#define RFU_A0_SetDigitalInput()   ( TRISASET = (1 << 0) )
/**
  @Summary
    Configures the GPIO pin, RA0, as an output.

  @Description
    Configures the GPIO pin, RA0, as an output.

  @Preconditions
    None.
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#define RFU_A0_SetDigitalOutput()   ( TRISACLR = (1 << 0) )
/**
  @Summary
    Sets the GPIO pin, RA1, high using LATA1.

  @Description
    Sets the GPIO pin, RA1, high using LATA1.

  @Preconditions
    The RA1 must be set to an output.
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#define RFU_A1_SetHigh()          ( LATASET = (1 << 1) )
/**
  @Summary
    Sets the GPIO pin, RA1, low using LATA1.

  @Description
    Sets the GPIO pin, RA1, low using LATA1.

  @Preconditions
    The RA1 must be set to an output.
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
/**
  @Summary
    Sets a value to the GPIO pin.

  @Description
    Sets or Resets the GPIO pin, RA1, low or high using LATA1.

  @Preconditions
    The RA1 must be set to an output.
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    None.

  @Param
    bool value; : value to be set to the GPIO pin.

  @Example
    <code>
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
/**
  @Summary
    Toggles the GPIO pin, RA1, using LATA1.

  @Description
    Toggles the GPIO pin, RA1, using LATA1.

  @Preconditions
    The RA1 must be set to an output.
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#define RFU_A1_Toggle()           ( LATAINV = (1 << 1) )
/**
  @Summary
    Reads the value of the GPIO pin, RA1.

  @Description
    Reads the value of the GPIO pin, RA1.

  @Preconditions
    None.
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    </code>

*/
#define RFU_A1_GetValue()         PORTAbits.RA1
/**
  @Summary
    Configures the GPIO pin, RA1, as an input.

  @Description
    Configures the GPIO pin, RA1, as an input.

  @Preconditions
    None.
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#define RFU_A1_SetDigitalInput()   ( TRISASET = (1 << 1) )
/**
  @Summary
    Configures the GPIO pin, RA1, as an output.

  @Description
    Configures the GPIO pin, RA1, as an output.

  @Preconditions
    None.
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#define RFU_A1_SetDigitalOutput()   ( TRISACLR = (1 << 1) )
/**
  @Summary
    Sets the GPIO pin, RA4, high using LATA4.

  @Description
    Sets the GPIO pin, RA4, high using LATA4.

  @Preconditions
    The RA4 must be set to an output.
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#define BOOT_N_SetHigh()          ( LATASET = (1 << 4) )
/**
  @Summary
    Sets the GPIO pin, RA4, low using LATA4.

  @Description
    Sets the GPIO pin, RA4, low using LATA4.

  @Preconditions
    The RA4 must be set to an output.
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
/**
  @Summary
    Sets a value to the GPIO pin.

  @Description
    Sets or Resets the GPIO pin, RA4, low or high using LATA4.

  @Preconditions
    The RA4 must be set to an output.
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    None.

  @Param
    bool value; : value to be set to the GPIO pin.

  @Example
    <code>
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
/**
  @Summary
    Toggles the GPIO pin, RA4, using LATA4.

  @Description
    Toggles the GPIO pin, RA4, using LATA4.

  @Preconditions
    The RA4 must be set to an output.
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#define BOOT_N_Toggle()           ( LATAINV = (1 << 4) )
/**
  @Summary
    Reads the value of the GPIO pin, RA4.

  @Description
    Reads the value of the GPIO pin, RA4.

  @Preconditions
    None.
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    </code>

*/
#define BOOT_N_GetValue()         PORTAbits.RA4
/**
  @Summary
    Configures the GPIO pin, RA4, as an input.

  @Description
    Configures the GPIO pin, RA4, as an input.

  @Preconditions
    None.
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#define BOOT_N_SetDigitalInput()   ( TRISASET = (1 << 4) )
/**
  @Summary
    Configures the GPIO pin, RA4, as an output.

  @Description
    Configures the GPIO pin, RA4, as an output.

  @Preconditions
    None.
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#define BOOT_N_SetDigitalOutput()   ( TRISACLR = (1 << 4) )
/**
  @Summary
    Sets the GPIO pin, RB0, high using LATB0.

  @Description
    Sets the GPIO pin, RB0, high using LATB0.

  @Preconditions
    The RB0 must be set to an output.
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#define PG_PGD_SetHigh()          ( LATBSET = (1 << 0) )
/**
  @Summary
    Sets the GPIO pin, RB0, low using LATB0.

  @Description
    Sets the GPIO pin, RB0, low using LATB0.

  @Preconditions
    The RB0 must be set to an output.
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
/**
  @Summary
    Sets a value to the GPIO pin.

  @Description
    Sets or Resets the GPIO pin, RB0, low or high using LATB0.

  @Preconditions
    The RB0 must be set to an output.
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    None.

  @Param
    bool value; : value to be set to the GPIO pin.

  @Example
    <code>
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
/**
  @Summary
    Toggles the GPIO pin, RB0, using LATB0.

  @Description
    Toggles the GPIO pin, RB0, using LATB0.

  @Preconditions
    The RB0 must be set to an output.
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#define PG_PGD_Toggle()           ( LATBINV = (1 << 0) )
/**
  @Summary
    Reads the value of the GPIO pin, RB0.

  @Description
    Reads the value of the GPIO pin, RB0.

  @Preconditions
    None.
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    </code>

*/
#define PG_PGD_GetValue()         PORTBbits.RB0
/**
  @Summary
    Configures the GPIO pin, RB0, as an input.

  @Description
    Configures the GPIO pin, RB0, as an input.

  @Preconditions
    None.
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#define PG_PGD_SetDigitalInput()   ( TRISBSET = (1 << 0) )
/**
  @Summary
    Configures the GPIO pin, RB0, as an output.

  @Description
    Configures the GPIO pin, RB0, as an output.

  @Preconditions
    None.
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#define PG_PGD_SetDigitalOutput()   ( TRISBCLR = (1 << 0) )
/**
  @Summary
    Sets the GPIO pin, RB1, high using LATB1.

  @Description
    Sets the GPIO pin, RB1, high using LATB1.

  @Preconditions
    The RB1 must be set to an output.
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#define PG_PGC_SetHigh()          ( LATBSET = (1 << 1) )
/**
  @Summary
    Sets the GPIO pin, RB1, low using LATB1.

  @Description
    Sets the GPIO pin, RB1, low using LATB1.

  @Preconditions
    The RB1 must be set to an output.
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
/**
  @Summary
    Sets a value to the GPIO pin.

  @Description
    Sets or Resets the GPIO pin, RB1, low or high using LATB1.

  @Preconditions
    The RB1 must be set to an output.
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    None.

  @Param
    bool value; : value to be set to the GPIO pin.

  @Example
    <code>
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
/**
  @Summary
    Toggles the GPIO pin, RB1, using LATB1.

  @Description
    Toggles the GPIO pin, RB1, using LATB1.

  @Preconditions
    The RB1 must be set to an output.
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#define PG_PGC_Toggle()           ( LATBINV = (1 << 1) )
/**
  @Summary
    Reads the value of the GPIO pin, RB1.

  @Description
    Reads the value of the GPIO pin, RB1.

  @Preconditions
    None.
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    </code>

*/
#define PG_PGC_GetValue()         PORTBbits.RB1
/**
  @Summary
    Configures the GPIO pin, RB1, as an input.

  @Description
    Configures the GPIO pin, RB1, as an input.

  @Preconditions
    None.
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#define PG_PGC_SetDigitalInput()   ( TRISBSET = (1 << 1) )
/**
  @Summary
    Configures the GPIO pin, RB1, as an output.

  @Description
    Configures the GPIO pin, RB1, as an output.

  @Preconditions
    None.
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#define PG_PGC_SetDigitalOutput()   ( TRISBCLR = (1 << 1) )
/**
  @Summary
    Sets the GPIO pin, RB13, high using LATB13.

  @Description
    Sets the GPIO pin, RB13, high using LATB13.

  @Preconditions
    The RB13 must be set to an output.
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#define RLED_EXT_SetHigh()          ( LATBSET = (1 << 13) )
/**
  @Summary
    Sets the GPIO pin, RB13, low using LATB13.

  @Description
    Sets the GPIO pin, RB13, low using LATB13.

  @Preconditions
    The RB13 must be set to an output.
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
/**
  @Summary
    Sets a value to the GPIO pin.

  @Description
    Sets or Resets the GPIO pin, RB13, low or high using LATB13.

  @Preconditions
    The RB13 must be set to an output.
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    None.

  @Param
    bool value; : value to be set to the GPIO pin.

  @Example
    <code>
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
/**
  @Summary
    Toggles the GPIO pin, RB13, using LATB13.

  @Description
    Toggles the GPIO pin, RB13, using LATB13.

  @Preconditions
    The RB13 must be set to an output.
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#define RLED_EXT_Toggle()           ( LATBINV = (1 << 13) )
/**
  @Summary
    Reads the value of the GPIO pin, RB13.

  @Description
    Reads the value of the GPIO pin, RB13.

  @Preconditions
    None.
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#define RLED_EXT_GetValue()         PORTBbits.RB13
/**
  @Summary
    Configures the GPIO pin, RB13, as an input.
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

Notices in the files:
FW/PG.X/mcc_generated_files/pin_manager.h:
(c) 2020 Microchip Technology Inc. and its subsidiaries. You may use this
FW/TG.X/mcc_generated_files/pin_manager.h:
(c) 2018 Microchip Technology Inc. and its subsidiaries.
